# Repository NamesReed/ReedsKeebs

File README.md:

# ReedsKeebs
This repository contains all working firmware for my boards and design files I have made public.  

Join my discord for help: https://discord.gg/JtBQ8nmr7R

If you have a ProMicro or similar, you will find instructions for flashing within the Alish40 QMK Firmware directory.

# KMK firmware is officially supported on the KB2040, to change your keymap, you must edit a text file, this can be done on the fly and does not require reflashing.

If you have a KB2040 and an Alish board, you can find the QMK/Vial install guide within the QMK Firmware directory.

If you have a KB2040 and an Alish board, You can find the install guide within the KMK Firmware directory.  
### To boil it down simply, the QMK/Vial KB2040 firmware is experimental, and not officially supported. This grants you the use of changing your keymap with the Vial GUI. 
## Use QMK KB2040 at your own risk.

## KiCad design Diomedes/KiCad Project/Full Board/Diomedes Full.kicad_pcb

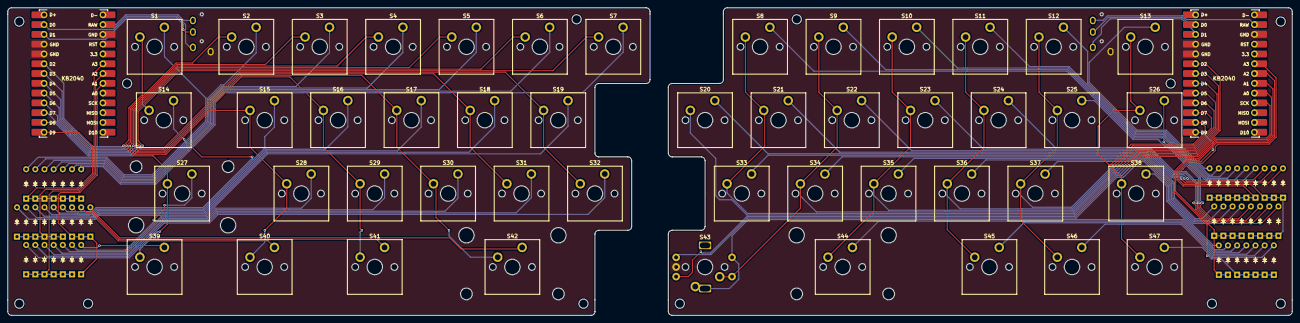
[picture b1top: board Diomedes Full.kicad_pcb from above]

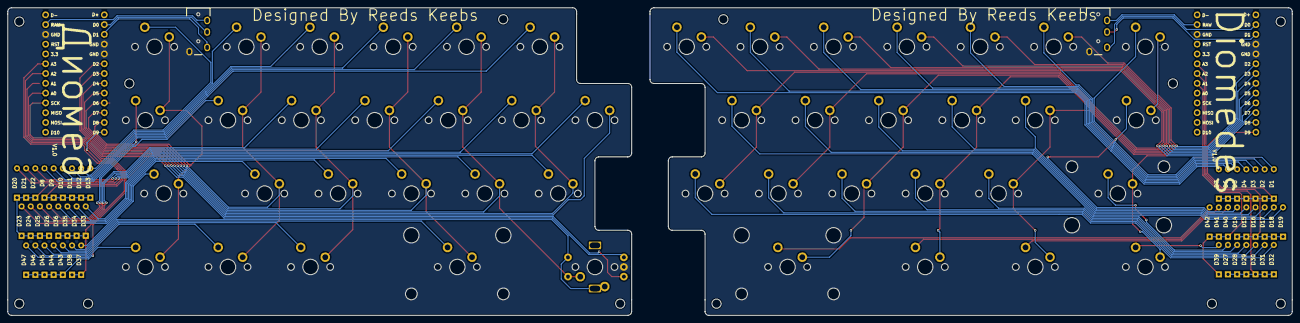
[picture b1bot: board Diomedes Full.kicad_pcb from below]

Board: 2 copper layers, 333.4 x 79.8 mm, 101 parts (2 on the bottom side), 78 nets.

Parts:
D1, D2, D3, D4, D5, D6, D7, D8, D9, D10, D11, D12, D13, D14, D15, D16, D17, D18, D19, D20, D21, D22, D23, D24, D25, D26, D27, D28, D29, D30, D31, D32, D33, D34, D35, D36, D37, D38, D39, D40, D41, D42, D43, D44, D45, D46, D47: Diode_DO-35
MC1, MC2: Adafruit_KB2040_SMD
S1, S13, S39, S40, S41: MX_PCB_1.50u
S2, S3, S4, S5, S6, S7, S8, S9, S10, S11, S12, S15, S16, S17, S18, S19, S20, S21, S22, S23, S24, S25, S28, S29, S30, S31, S32, S33, S34, S35, S36, S37, S46: MX_PCB_1.00u
S14, S38: MX_PCB_1.75u
S26, S45, S47: MX_PCB_1.25u
S27, S42: MX_PCB_2.25u
S43: RotaryEncoder_Switch; Encoder_EC11_MX_Combo
S44: MX_PCB_2.75u
STAB1, STAB2, STAB3: Stabilizer_MX_2.00u
T1, T2: TRRS; 4Pole-TRRS-PJ-320A

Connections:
/Col 1: MC1.6 (2/PD1), S1.1, S14.1, S27.1, S39.1
/Col 1B: MC2.6 (2/PD1), S20.1
/Col 2: MC1.7 (3/PD0), S2.1, S15.1, S28.1, S40.1
/Col 2B: MC2.7 (3/PD0), S8.1, S21.1, S33.1
/Col 3: MC1.8 (4/PD4), S3.1, S16.1, S29.1, S41.1
/Col 3B: MC2.8 (4/PD4), S9.1, S22.1, S34.1, S43.S1
/Col 4: MC1.9 (5/PC6), S4.1, S17.1, S30.1, S42.1
/Col 4B: MC2.9 (5/PC6), S10.1, S23.1, S35.1, S44.1
/Col 5: MC1.10 (6/PD7), S5.1, S18.1, S31.1
/Col 5B: MC2.10 (6/PD7), S11.1, S24.1, S36.1, S45.1
/Col 6: MC1.11 (7/PE6), S6.1, S19.1, S32.1
/Col 6B: MC2.11 (7/PE6), S12.1, S25.1, S37.1, S46.1
/Col 7: MC1.12 (8/PB4), S7.1
/Col 7B: MC2.12 (8/PB4), S13.1, S26.1, S38.1, S47.1
/ENC_A: MC2.22 (A0/PF7), S43.A
/ENC_B: MC2.23 (15/PB1), S43.B
/RAW_L: MC1.15 (RAW), T1.4 (RING2)
/RAW_R: MC2.15 (RAW), T2.4 (RING2)
/RX_L: MC1.3 (RX1/PD2), T1.3 (RING1)
/RX_R: MC2.2 (TX0/PD3), T2.3 (RING1)
/Row 1: D1.1 (K), D2.1 (K), D3.1 (K), D4.1 (K), D5.1 (K), D6.1 (K), D7.1 (K), MC1.13 (9/PB5)
/Row 1B: D8.1 (K), D9.1 (K), D10.1 (K), D11.1 (K), D12.1 (K), D13.1 (K), MC2.13 (9/PB5)
/Row 2: D14.1 (K), D15.1 (K), D16.1 (K), D17.1 (K), D18.1 (K), D19.1 (K), MC1.19 (A3/PF4)
/Row 2B: D20.1 (K), D21.1 (K), D22.1 (K), D23.1 (K), D24.1 (K), D25.1 (K), D26.1 (K), MC2.19 (A3/PF4)
/Row 3: D27.1 (K), D28.1 (K), D29.1 (K), D30.1 (K), D31.1 (K), D32.1 (K), MC1.20 (A2/PF5)
/Row 3B: D33.1 (K), D34.1 (K), D35.1 (K), D36.1 (K), D37.1 (K), D38.1 (K), MC2.20 (A2/PF5)
/Row 4: D39.1 (K), D40.1 (K), D41.1 (K), D42.1 (K), MC1.21 (A1/PF6)
/Row 4B: D43.1 (K), D44.1 (K), D45.1 (K), D46.1 (K), D47.1 (K), MC2.21 (A1/PF6)
/TX_L: MC1.2 (TX0/PD3), T1.2 (TIP)
/TX_R: MC2.3 (RX1/PD2), T2.2 (TIP)
GND: MC1.4 (GND), MC1.5 (GND), MC1.16 (GND), MC2.4 (GND), MC2.5 (GND), MC2.16 (GND), S43.C, T1.1 (SLEEVE), T2.1 (SLEEVE)
unnamed: D1.2 (A), S1.2
unnamed: D2.2 (A), S2.2
unnamed: D3.2 (A), S3.2
unnamed: D4.2 (A), S4.2
unnamed: D5.2 (A), S5.2
unnamed: D6.2 (A), S6.2
unnamed: D7.2 (A), S7.2
unnamed: D8.2 (A), S8.2
unnamed: D9.2 (A), S9.2
unnamed: D10.2 (A), S10.2
unnamed: D11.2 (A), S11.2
unnamed: D12.2 (A), S12.2
unnamed: D13.2 (A), S13.2
unnamed: D14.2 (A), S14.2
unnamed: D15.2 (A), S15.2
unnamed: D16.2 (A), S16.2
unnamed: D17.2 (A), S17.2
unnamed: D18.2 (A), S18.2
unnamed: D19.2 (A), S19.2
unnamed: D20.2 (A), S20.2
unnamed: D21.2 (A), S21.2
unnamed: D22.2 (A), S22.2
unnamed: D23.2 (A), S23.2
unnamed: D24.2 (A), S24.2
unnamed: D25.2 (A), S25.2
unnamed: D26.2 (A), S26.2
unnamed: D27.2 (A), S27.2
unnamed: D28.2 (A), S28.2
unnamed: D29.2 (A), S29.2
unnamed: D30.2 (A), S30.2
unnamed: D31.2 (A), S31.2
unnamed: D32.2 (A), S32.2
unnamed: D33.2 (A), S33.2
unnamed: D34.2 (A), S34.2
unnamed: D35.2 (A), S35.2
unnamed: D36.2 (A), S36.2
unnamed: D37.2 (A), S37.2
unnamed: D38.2 (A), S38.2
unnamed: D39.2 (A), S39.2
unnamed: D40.2 (A), S40.2
unnamed: D41.2 (A), S41.2
unnamed: D42.2 (A), S42.2
unnamed: D43.2 (A), S43.S2
unnamed: D44.2 (A), S44.2
unnamed: D45.2 (A), S45.2
unnamed: D46.2 (A), S46.2
unnamed: D47.2 (A), S47.2

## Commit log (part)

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2022-03-10 Add Alish KMK firmware
2022-03-10 Added code.py file
2022-03-13 Added vial firmware source for troubleshooting
2022-03-13 Deleted directory, troubleshooting resolved
2022-03-13 Added Vial Hex for Pro Micro boards
2022-03-13 Deleting Vial hex
    Vial.json file was not properly configured
2022-03-13 Added fixed vial.hex
    Properly configured vial.json to properly display layout within vial
2022-03-13 Added Alish40 QMK source code
2022-03-13 Added a line for pro micro instructions
2022-03-13 Created instructions for flashing Pro Micro
2022-03-13 Added link to QMK Toolbox
2022-03-14 Updated keymap to include question mark.
    Added KC.SLASH to layer 1 and removed KC.UP so that right shift still functioned within layer 1.
2022-03-15 Fixed instructions.
2022-03-26 Added updated precompiled vial firmware.
    Included encoder, and split/big enter layout options.
2022-03-27 Added disclaimer about KMK
2022-04-03 Replaced code.py with main.py
    improved default keymap, fixed encoder pins and direction.
2022-04-03 Changed code.py reference to say main.py
2022-04-03 Added KB2040 Vial/QMK firmware
2022-04-03 Added readme to KB2040 folder
2022-04-03 Create KB2040 Firmware
2022-04-03 Added KB2040 Vial instructions
2022-04-03 Moving KMK readme to correct directory
2022-04-04 Added Pro Micro firmware and source
2022-04-14 scanners instead of matrix
2022-04-14 Update main.py
    update kmk.matrix to kmk.scanners
2022-04-15 formatting and minor edits
2022-05-16 Waxwing V1 Firmware
    Firmware for Waxwing V1, Includes standard pro micro Vial hex and source, KB2040 Vial UF2 and source, and KB2040 KMK.
2022-12-17 Make keymap peg compatible
    V1, untested
2023-01-09 Update Alish Firmware to GB Version
    Mark old firmware for v1.0 through 1.1 as deprecated, and upload section for v1.3+ firmware.
2023-01-11 copied readme to v1.3 and added shell script for linux users
2023-01-12 Apply suggestions from code review
